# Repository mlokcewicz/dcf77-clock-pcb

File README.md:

# dcf77-clock-pcb

**DCF77-controlled** radio clock PCB based on the **ATmega88** microcontroller, **MAS6181B** AM receiver, and **DS1307** RTC.

**Capabilities:**
* Time and date display
* Alarm handling
* Manual date and time setting
* Automatic periodic synchronization with the DCF77 signal
* Time synchronization status display
* Time zone configuration
* DCF77 signal parameters preview during synchronization
* Time and date data available over the serial port
* Time and date retention powered by a CR2032 battery
  
**Hardware:**
* ATmega88 MCU
* MAS6181B DCF77 receiver
* DS1307 RTC + CR2032
* 2x16 HD44760 LCD
* Rotary Encoder + Button + LED + Buzzer

**Firmware:**
* C11
* Custom MCU peripheral and external circuit drivers

## Tools
* Autodesk EAGLE v9.6.2

## External links
* Firmware repository: https://github.com/mlokcewicz/dcf77-clock

## License
This project is licensed under the CERN Open Hardware Licence Version 2 - Permissive - see the [LICENSE](./LICENSE) file for details.

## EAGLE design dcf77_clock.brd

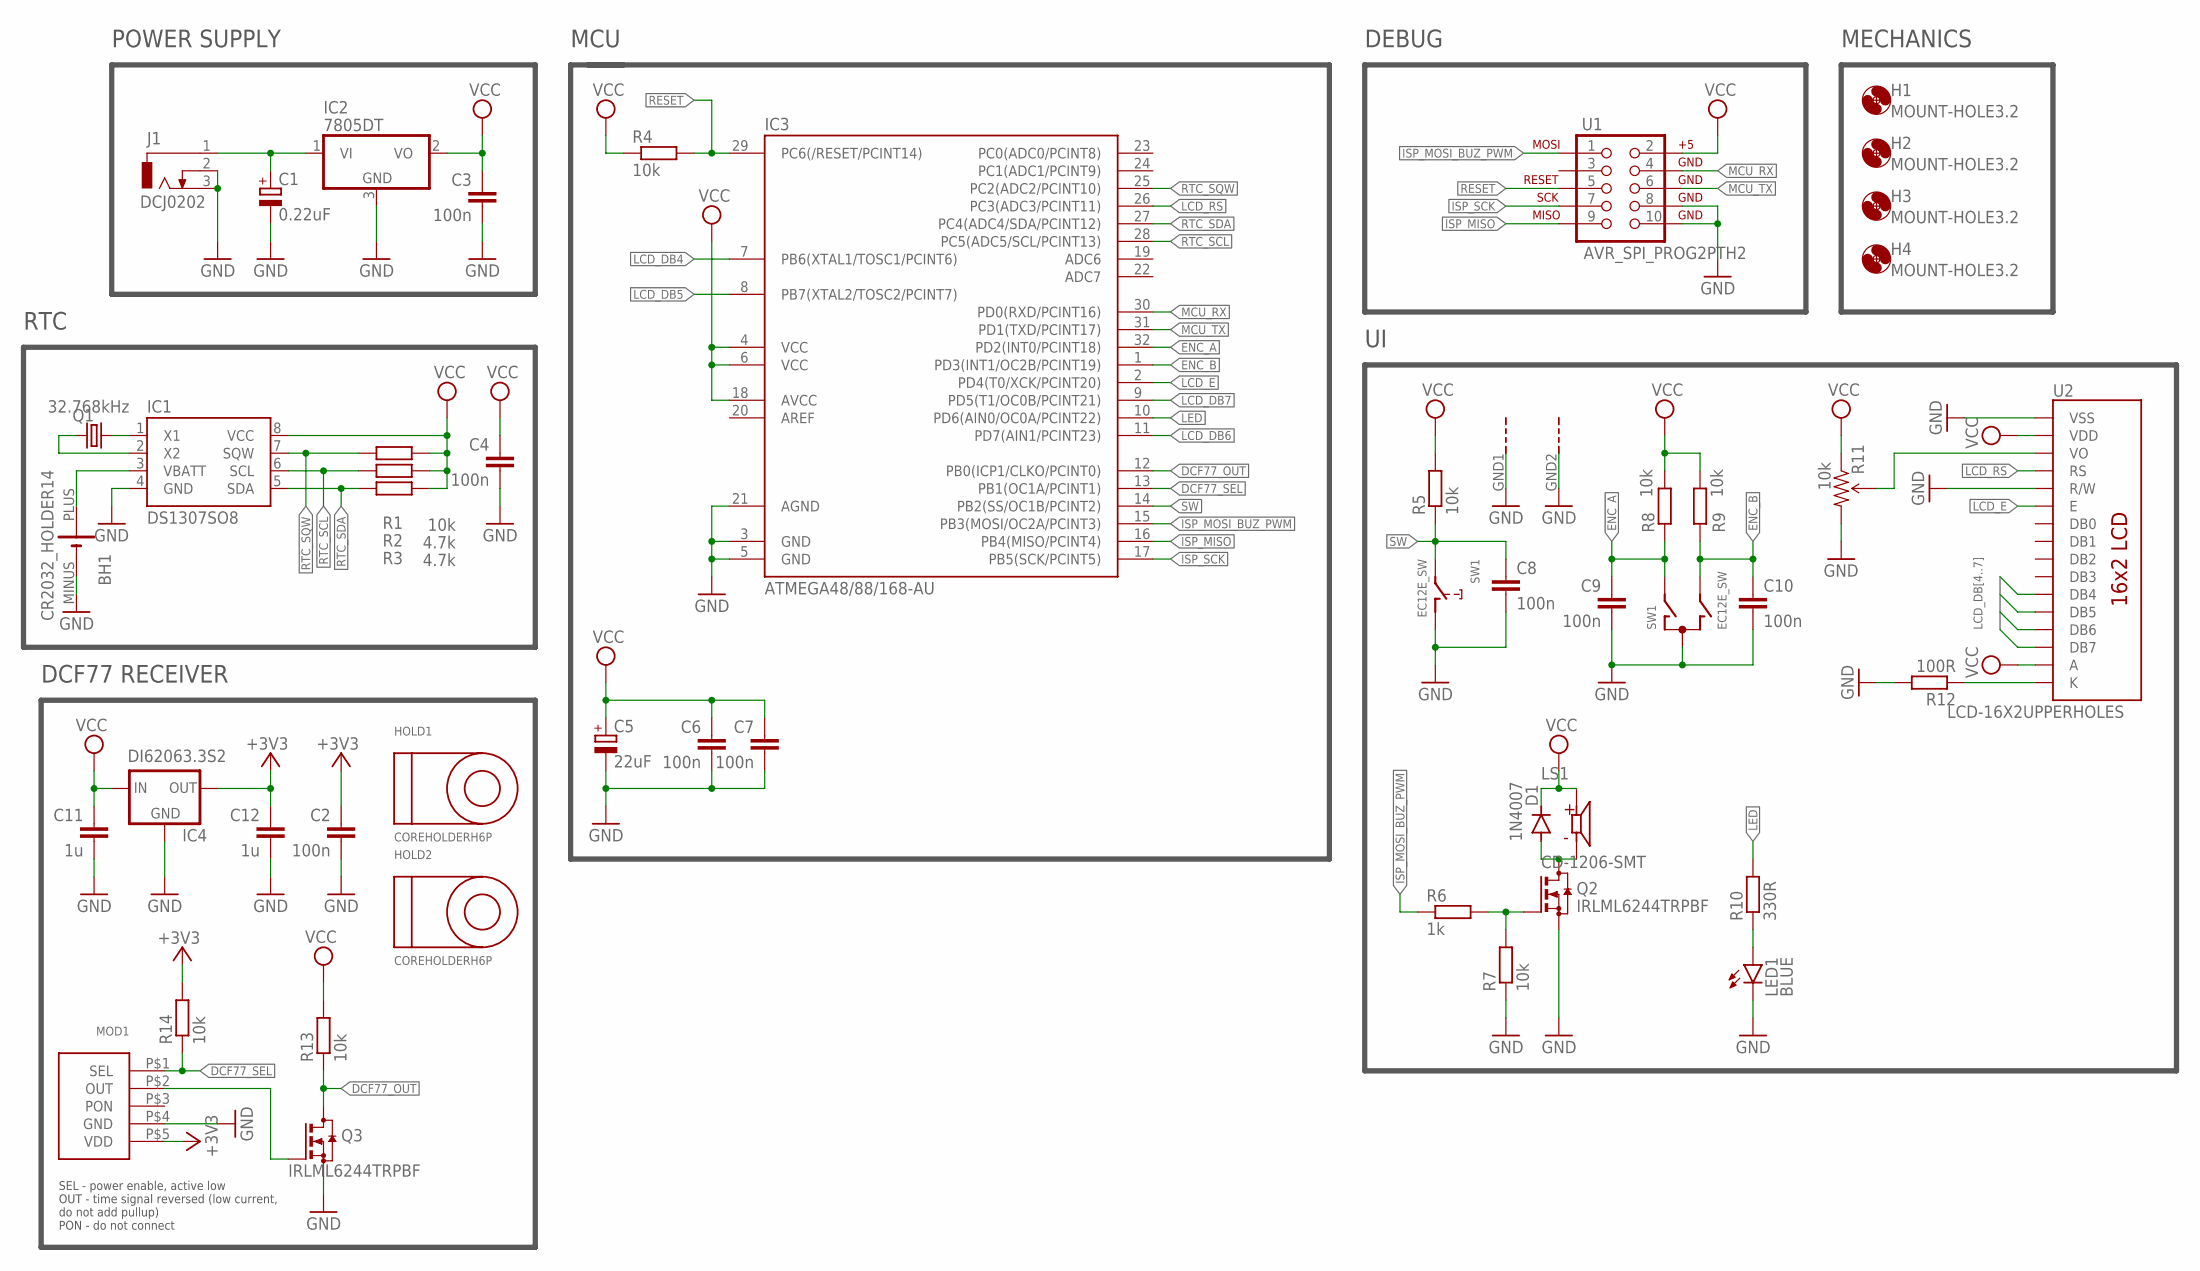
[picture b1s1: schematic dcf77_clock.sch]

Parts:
BH1: CR2032_HOLDER14; CONNFLY-DS1092-14-B6P
C1: 0.22uF; SMC_Z
C2, C3, C4, C6, C7, C8, C9, C10: 100n; C0805K
C5: 22uF; UD-4X5,8_NICHICON
C11, C12: 1u; C0805K
D1: 1N4007; SOD123
H1, H2, H3, H4: MOUNT-HOLE3.2; 3,2
HOLD1, HOLD2: COREHOLDERH6P; H6P
IC1: DS1307SO8; SO08
IC2: 7805DT; TO252
IC3: ATMEGA48/88/168-AU; TQFP32-08
IC4: DI62063.3S2; SOT23
J1: DCJ0202
LED1: BLUE; CHIP-LED0805
LS1: CD-1206-SMT; CUI_CD-1206-SMT
MOD1: DCF77MODULE; DCF77MOD
Q1: 32.768kHz; MM20SS
Q2, Q3: IRLML6244TRPBF; SOT23
R1, R4, R5, R7, R8, R9, R13, R14: 10k; M0805
R2, R3: 4.7k; M0805
R6: 1k; M0805
R10: 330R; M0805
R11: 10k; TRIM_POT_PTH
R12: 100R; M0805
SW1: EC12E_SW; ALPS_EC12E_SW
U1: AVR_SPI_PROG2PTH2; 2X5-SHROUDED
U2: LCD-16X2UPPERHOLES; LCD-16X2_UPPER_HOLES

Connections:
+3V3: C2.1, C12.1, IC4.2 (OUT), MOD1.P$5 (VDD), R14.2
DCF77_OUT: IC3.12 (PB0(ICP1/CLKO/PCINT0)), Q3.3 (D), R13.1
DCF77_SEL: IC3.13 (PB1(OC1A/PCINT1)), MOD1.P$1 (SEL), R14.1
ENC_A: C9.1, IC3.32 (PD2(INT0/PCINT18)), R8.1, SW1.A
ENC_B: C10.1, IC3.1 (PD3(INT1/OC2B/PCINT19)), R9.1, SW1.B
GND: BH1.MINUS, C1.-, C2.2, C3.2, C4.2, C5.-, C6.2, C7.2, C8.2, C9.2, C10.2, C11.2, C12.2, IC1.4 (GND), IC2.3 (GND), IC3.3 (GND), IC3.5 (GND), IC3.21 (AGND), IC4.1 (GND), J1.2, J1.3, LED1.C, MOD1.P$4 (GND), Q2.2 (S), Q3.2 (S), R7.1, R11.3 (CW), R12.2, SW1.C, SW1.D (1), SW1.GND1 (G), SW1.GND2 (G), U1.8, U1.10, U2.1 (VSS), U2.5 (R/W)
ISP_MISO: IC3.16 (PB4(MISO/PCINT4)), U1.9
ISP_MOSI_BUZ_PWM: IC3.15 (PB3(MOSI/OC2A/PCINT3)), R6.1, U1.1
ISP_SCK: IC3.17 (PB5(SCK/PCINT5)), U1.7
LCD_DB4: IC3.7 (PB6(XTAL1/TOSC1/PCINT6)), U2.11 (DB4)
LCD_DB5: IC3.8 (PB7(XTAL2/TOSC2/PCINT7)), U2.12 (DB5)
LCD_DB6: IC3.11 (PD7(AIN1/PCINT23)), U2.13 (DB6)
LCD_DB7: IC3.9 (PD5(T1/OC0B/PCINT21)), U2.14 (DB7)
LCD_E: IC3.2 (PD4(T0/XCK/PCINT20)), U2.6 (E)
LCD_RS: IC3.26 (PC3(ADC3/PCINT11)), U2.4 (RS)
LED: IC3.10 (PD6(AIN0/OC0A/PCINT22)), R10.2
MCU_RX: IC3.30 (PD0(RXD/PCINT16)), U1.4
MCU_TX: IC3.31 (PD1(TXD/PCINT17)), U1.6
unnamed: C1.+, IC2.1 (VI), J1.1
unnamed: D1.A, LS1.M, Q2.3 (D)
unnamed: Q2.1 (G), R6.2, R7.2
unnamed: LED1.A, R10.1
unnamed: MOD1.P$2 (OUT), Q3.1 (G)
unnamed: R11.2 (WIPER), U2.3 (VO)
unnamed: R12.1, U2.16 (K)
unnamed: IC1.1 (X1), Q1.1
unnamed: IC1.2 (X2), Q1.4 (2)
unnamed: BH1.PLUS, IC1.3 (VBATT)
RESET: IC3.29 (PC6(/RESET/PCINT14)), R4.2, U1.5
RTC_SCL: IC1.6 (SCL), IC3.28 (PC5(ADC5/SCL/PCINT13)), R2.2
RTC_SDA: IC1.5 (SDA), IC3.27 (PC4(ADC4/SDA/PCINT12)), R3.2
RTC_SQW: IC1.7 (SQW), IC3.25 (PC2(ADC2/PCINT10)), R1.2
SW: C8.1, IC3.14 (PB2(SS/OC1B/PCINT2)), R5.1, SW1.E (2)
VCC: C3.1, C4.1, C5.+, C6.1, C7.1, C11.1, D1.C, IC1.8 (VCC), IC2.2 (VO), IC3.4 (VCC), IC3.6 (VCC), IC3.18 (AVCC), IC4.3 (IN), LS1.P, R1.1, R2.1, R3.1, R4.1, R5.2, R8.2, R9.2, R11.1 (CCW), R13.2, U1.2, U2.2 (VDD), U2.15 (A)

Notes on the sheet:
POWER SUPPLY
MCU
DEBUG
MECHANICS
RTC
DCF77 RECEIVER
SEL - power enable, active low OUT - time signal reversed (low current, do not add pullup) PON - do not connect

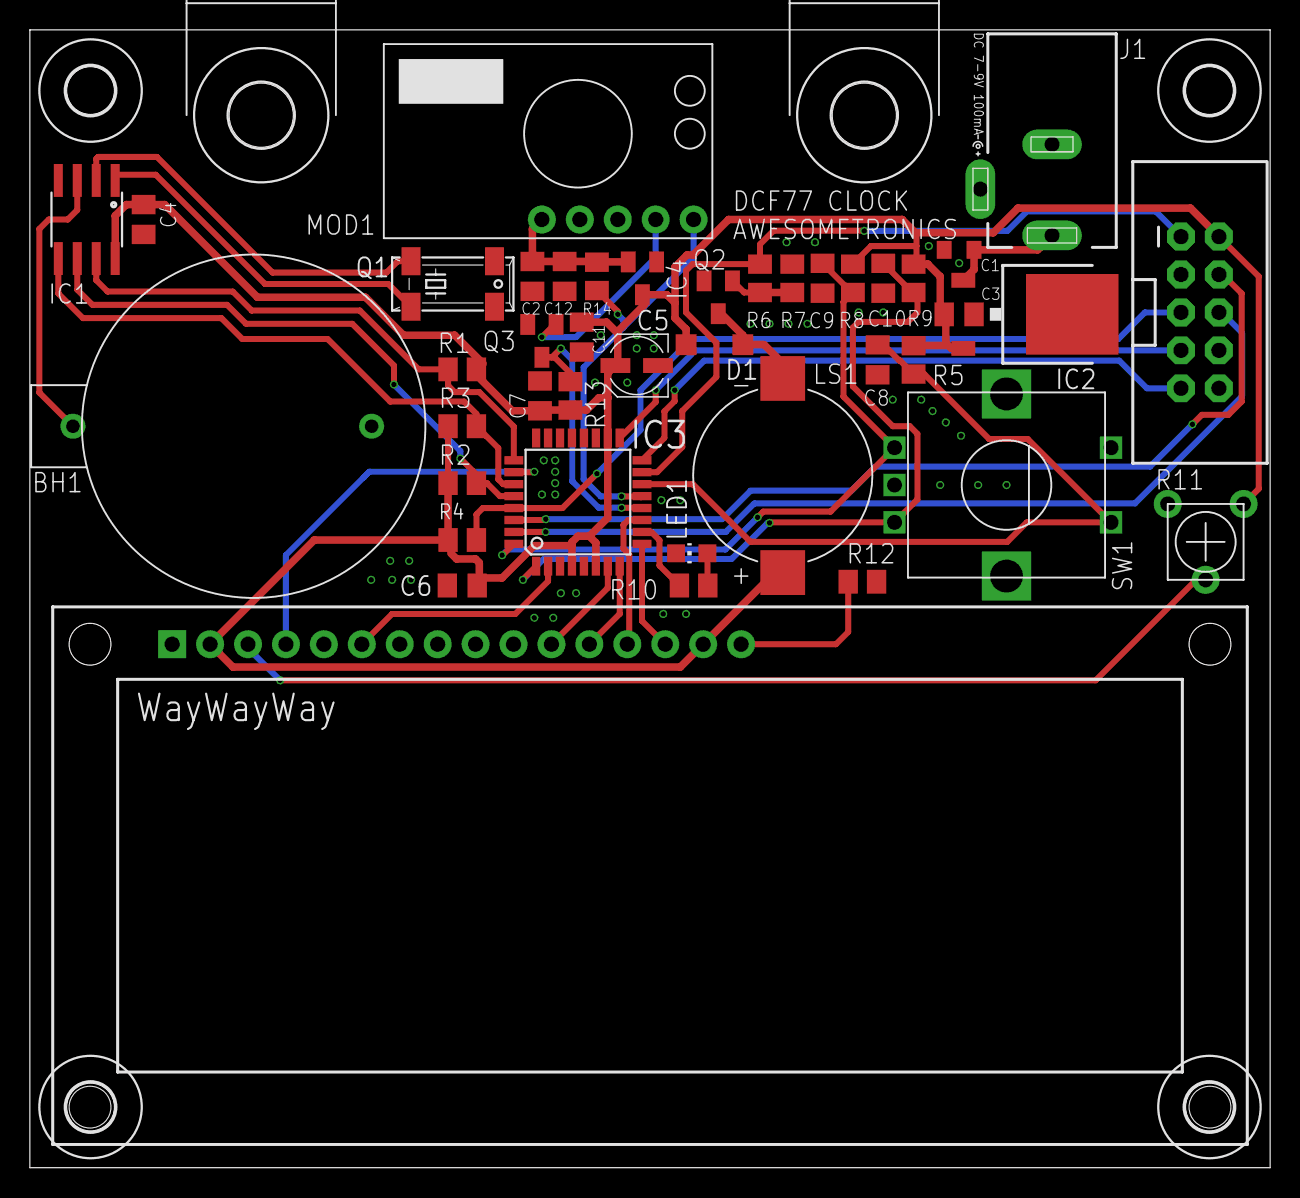
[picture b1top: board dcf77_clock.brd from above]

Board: 2 copper layers, 83.1 x 76.2 mm, 48 parts (0 on the bottom side), 34 nets.

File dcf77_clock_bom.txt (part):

Partlist exported from D:/Elektronika/Repozytoria/GitHub/hardware/dcf77-clock-pcb/dcf77_clock.sch at 09.04.2025 18:27

Qty Value              Device             Package               Parts                            Description                                  AVAILABILITY CUI_PURCHASE_URL                                                                                                                              DESCRIPTION                                                                      MF       MP             MPN          OC_FARNELL OC_NEWARK PACKAGE  POPULARITY PRICE SPICEPREFIX
1   0.22uF             CPOL-EUSMCZ        SMC_Z                 C1                               POLARIZED CAPACITOR, European symbol                                                                                                                                                                                                                                                                                                                        0                C          
1   100R               R-EU_M0805         M0805                 R12                              RESISTOR, European symbol                                                                                                                                                                                                                                                                                                                                   45               R          
8   100n               C-EUC0805K         C0805K                C2, C3, C4, C6, C7, C8, C9, C10  CAPACITOR, European symbol                                                                                                                                                                                                                                                                                                                                  52               C          
8   10k                R-EU_M0805         M0805                 R1, R4, R5, R7, R8, R9, R13, R14 RESISTOR, European symbol                                                                                                                                                                                                                                                                                                                                   45               R          
1   10k                TRIMPOTPTH         TRIM_POT_PTH          R11                                                                                                                                                                                                                                                                                                                                                                                                                      
1   1N4007             DIODE-SOD123       SOD123                D1                               DIODE                                                                                                                                                                                                                                                                                                                                                       22                          
1   1k                 R-EU_M0805         M0805                 R6                               RESISTOR, European symbol                                                                                                                                                                                                                                                                                                                                   45               R          
2   1u                 C-EUC0805K         C0805K                C11, C12                         CAPACITOR, European symbol                                                                                                                                                                                                                                                                                                                                  52               C          
1   22uF               CPOL-EUUD-4X5,8    UD-4X5,8_NICHICON     C5                               POLARIZED CAPACITOR, European symbol                                                                                                                                                                                                                                                                                                                        0                C          
1   32.768kHz          CRYSTALMM20SS      MM20SS                Q1                               CRYSTAL                                                                                                                                                                                                                                                                                                                       unknown    unknown            4                           
1   330R               R-EU_M0805         M0805                 R10                              RESISTOR, European symbol                                                                                                                                                                                                                                                                                                                                   45               R          
2   4.7k               R-EU_M0805         M0805                 R2, R3                           RESISTOR, European symbol                                                                                                                                                                                                                                                                                                                                   45               R          
1   7805DT             7805DT             TO252                 IC2                              Positive VOLTAGE REGULATOR                                                                                                                                                                                                                                                                                                                                  0                           
1   ATMEGA48/88/168-AU ATMEGA48/88/168-AU TQFP32-08             IC3                                                                                                                                                                                                                                                                                                                                                                                                                      
1   AVR_SPI_PROG2PTH2  AVR_SPI_PROG2PTH2  2X5-SHROUDED          U1                               AVR ICSP Header                                                                                                                                                                                                                                                                                                                                                                         
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
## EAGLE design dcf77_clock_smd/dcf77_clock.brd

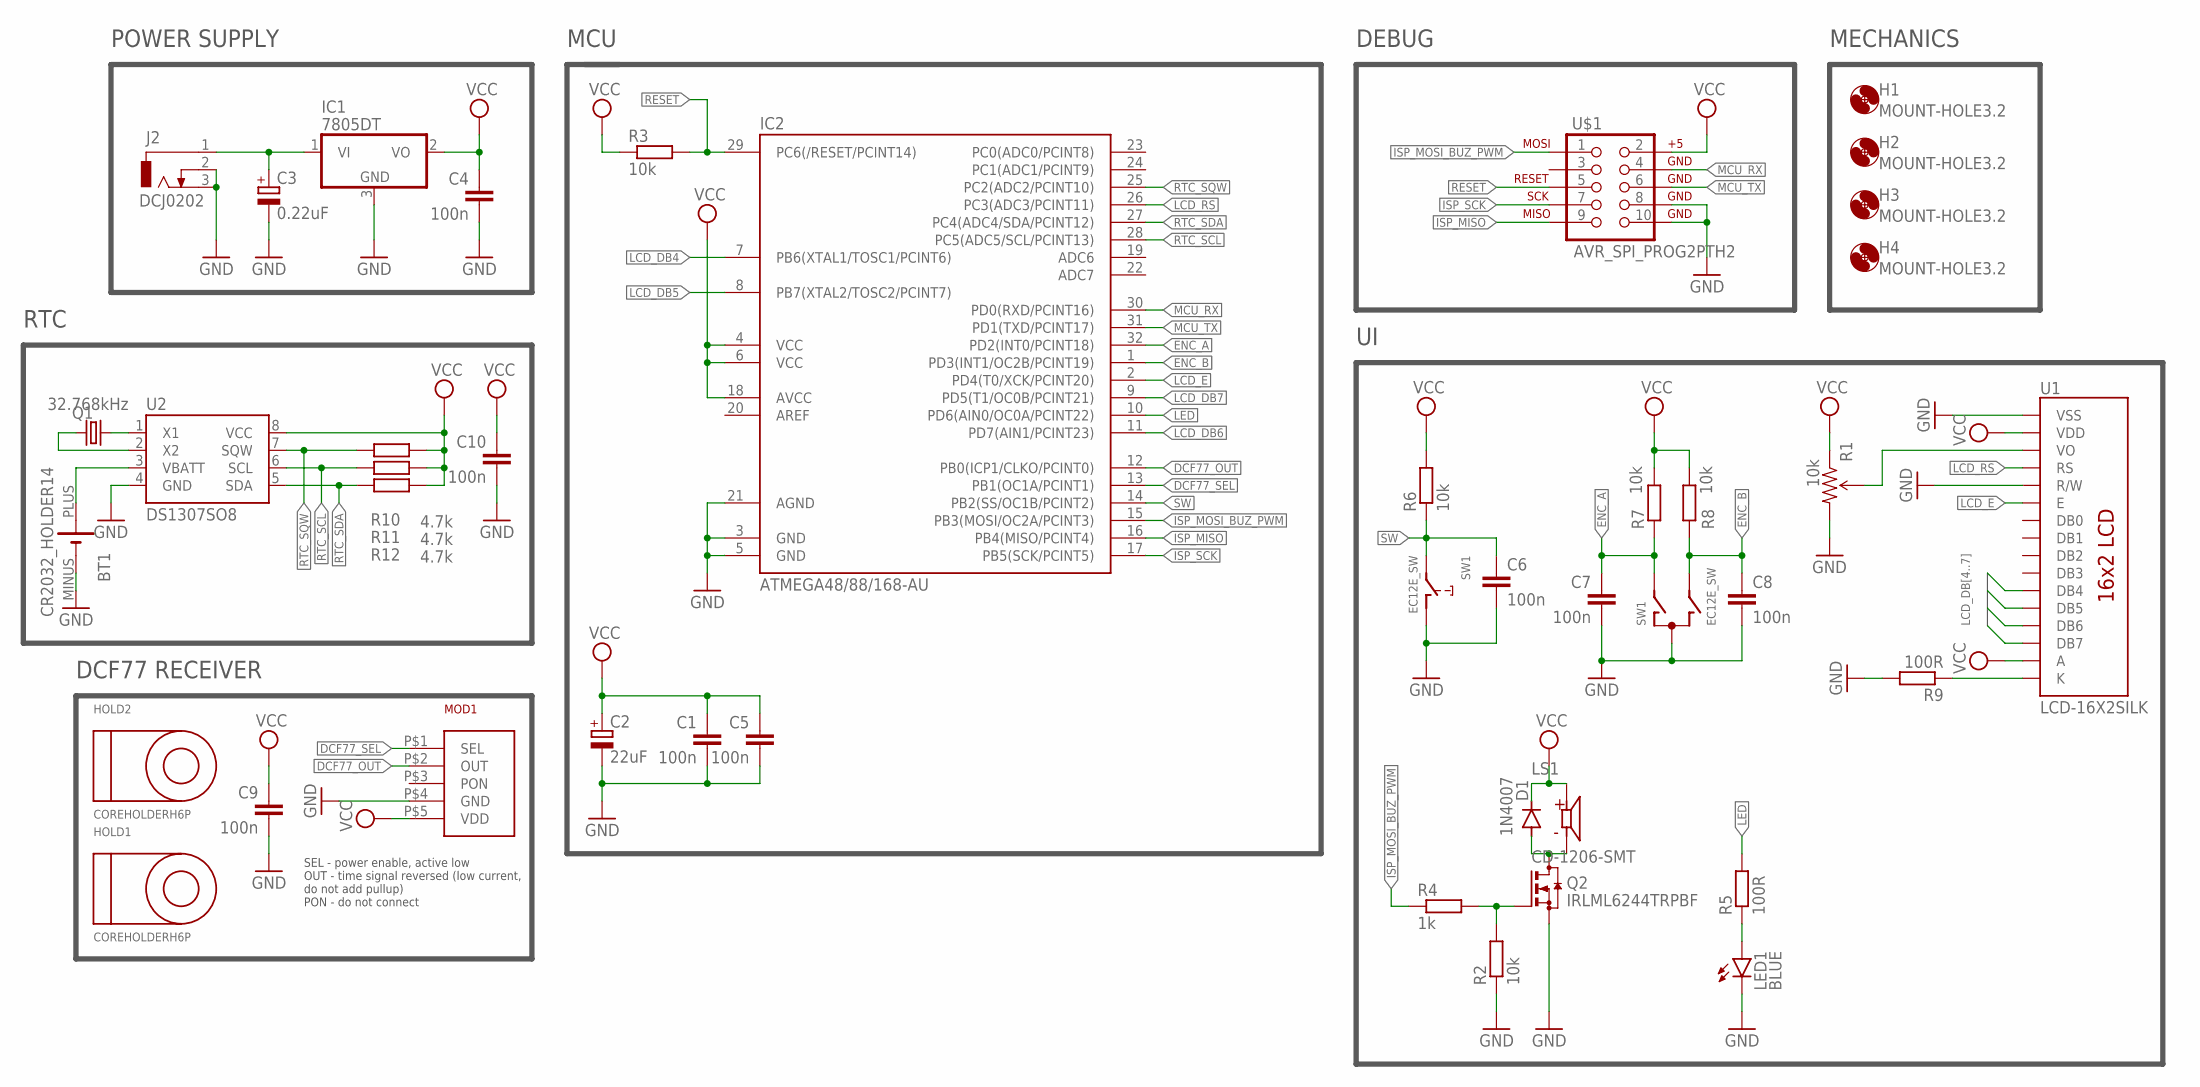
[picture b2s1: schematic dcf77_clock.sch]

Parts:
BT1: CR2032_HOLDER14; CONNFLY-DS1092-14-B6P
C1, C4, C5, C6, C7, C8, C9, C10: 100n; C0805K
C2: 22uF; UD-4X5,8_NICHICON
C3: 0.22uF; SMC_Z
D1: 1N4007; SOD123
H1, H2, H3, H4: MOUNT-HOLE3.2; 3,2
HOLD1, HOLD2: COREHOLDERH6P; H6P
IC1: 7805DT; TO252
IC2: ATMEGA48/88/168-AU; TQFP32-08
J2: DCJ0202
LED1: BLUE; CHIP-LED0805
LS1: CD-1206-SMT; CUI_CD-1206-SMT
MOD1: DCF77MODULE; DCF77MOD
Q1: 32.768kHz; MM20SS
Q2: IRLML6244TRPBF; SOT23
R1: 10k; TRIM_POT_PTH
R2, R3, R6, R7, R8: 10k; M0805
R4: 1k; M0805
R5, R9: 100R; M0805
R10, R11, R12: 4.7k; M0805
SW1: EC12E_SW; ALPS_EC12E_SW
U1: LCD-16X2SILK; LCD-16X2
U2: DS1307SO8; SO08
U$1: AVR_SPI_PROG2PTH2; 2X5-SHROUDED

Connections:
DCF77_OUT: IC2.12 (PB0(ICP1/CLKO/PCINT0)), MOD1.P$2 (OUT)
DCF77_SEL: IC2.13 (PB1(OC1A/PCINT1)), MOD1.P$1 (SEL)
ENC_A: C7.1, IC2.32 (PD2(INT0/PCINT18)), R7.1, SW1.A
ENC_B: C8.1, IC2.1 (PD3(INT1/OC2B/PCINT19)), R8.1, SW1.B
GND: BT1.MINUS, C1.2, C2.-, C3.-, C4.2, C5.2, C6.2, C7.2, C8.2, C9.2, C10.2, IC1.3 (GND), IC2.3 (GND), IC2.5 (GND), IC2.21 (AGND), J2.2, J2.3, LED1.C, MOD1.P$4 (GND), Q2.2 (S), R1.3 (CW), R2.1, R9.2, SW1.C, SW1.D (1), U1.1 (VSS), U1.5 (R/W), U2.4 (GND), U$1.8, U$1.10
ISP_MISO: IC2.16 (PB4(MISO/PCINT4)), U$1.9
ISP_MOSI_BUZ_PWM: IC2.15 (PB3(MOSI/OC2A/PCINT3)), R4.1, U$1.1
ISP_SCK: IC2.17 (PB5(SCK/PCINT5)), U$1.7
LCD_DB4: IC2.7 (PB6(XTAL1/TOSC1/PCINT6)), U1.11 (DB4)
LCD_DB5: IC2.8 (PB7(XTAL2/TOSC2/PCINT7)), U1.12 (DB5)
LCD_DB6: IC2.11 (PD7(AIN1/PCINT23)), U1.13 (DB6)
LCD_DB7: IC2.9 (PD5(T1/OC0B/PCINT21)), U1.14 (DB7)
LCD_E: IC2.2 (PD4(T0/XCK/PCINT20)), U1.6 (E)
LCD_RS: IC2.26 (PC3(ADC3/PCINT11)), U1.4 (RS)
LED: IC2.10 (PD6(AIN0/OC0A/PCINT22)), R5.2
MCU_RX: IC2.30 (PD0(RXD/PCINT16)), U$1.4
MCU_TX: IC2.31 (PD1(TXD/PCINT17)), U$1.6
unnamed: C3.+, IC1.1 (VI), J2.1
unnamed: D1.A, LS1.M, Q2.3 (D)
unnamed: Q2.1 (G), R2.2, R4.2
unnamed: LED1.A, R5.1
unnamed: R1.2 (WIPER), U1.3 (VO)
unnamed: R9.1, U1.16 (K)
unnamed: Q1.1, U2.1 (X1)
unnamed: Q1.4 (2), U2.2 (X2)
unnamed: BT1.PLUS, U2.3 (VBATT)
RESET: IC2.29 (PC6(/RESET/PCINT14)), R3.2, U$1.5
RTC_SCL: IC2.28 (PC5(ADC5/SCL/PCINT13)), R11.2, U2.6 (SCL)
RTC_SDA: IC2.27 (PC4(ADC4/SDA/PCINT12)), R12.2, U2.5 (SDA)
RTC_SQW: IC2.25 (PC2(ADC2/PCINT10)), R10.2, U2.7 (SQW)
SW: C6.1, IC2.14 (PB2(SS/OC1B/PCINT2)), R6.1, SW1.E (2)
VCC: C1.1, C2.+, C4.1, C5.1, C9.1, C10.1, D1.C, IC1.2 (VO), IC2.4 (VCC), IC2.6 (VCC), IC2.18 (AVCC), LS1.P, MOD1.P$5 (VDD), R1.1 (CCW), R3.1, R6.2, R7.2, R8.2, R10.1, R11.1, R12.1, U1.2 (VDD), U1.15 (A), U2.8 (VCC), U$1.2

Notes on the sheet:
POWER SUPPLY
MCU
DEBUG
MECHANICS
RTC
DCF77 RECEIVER
SEL - power enable, active low OUT - time signal reversed (low current, do not add pullup) PON - do not connect

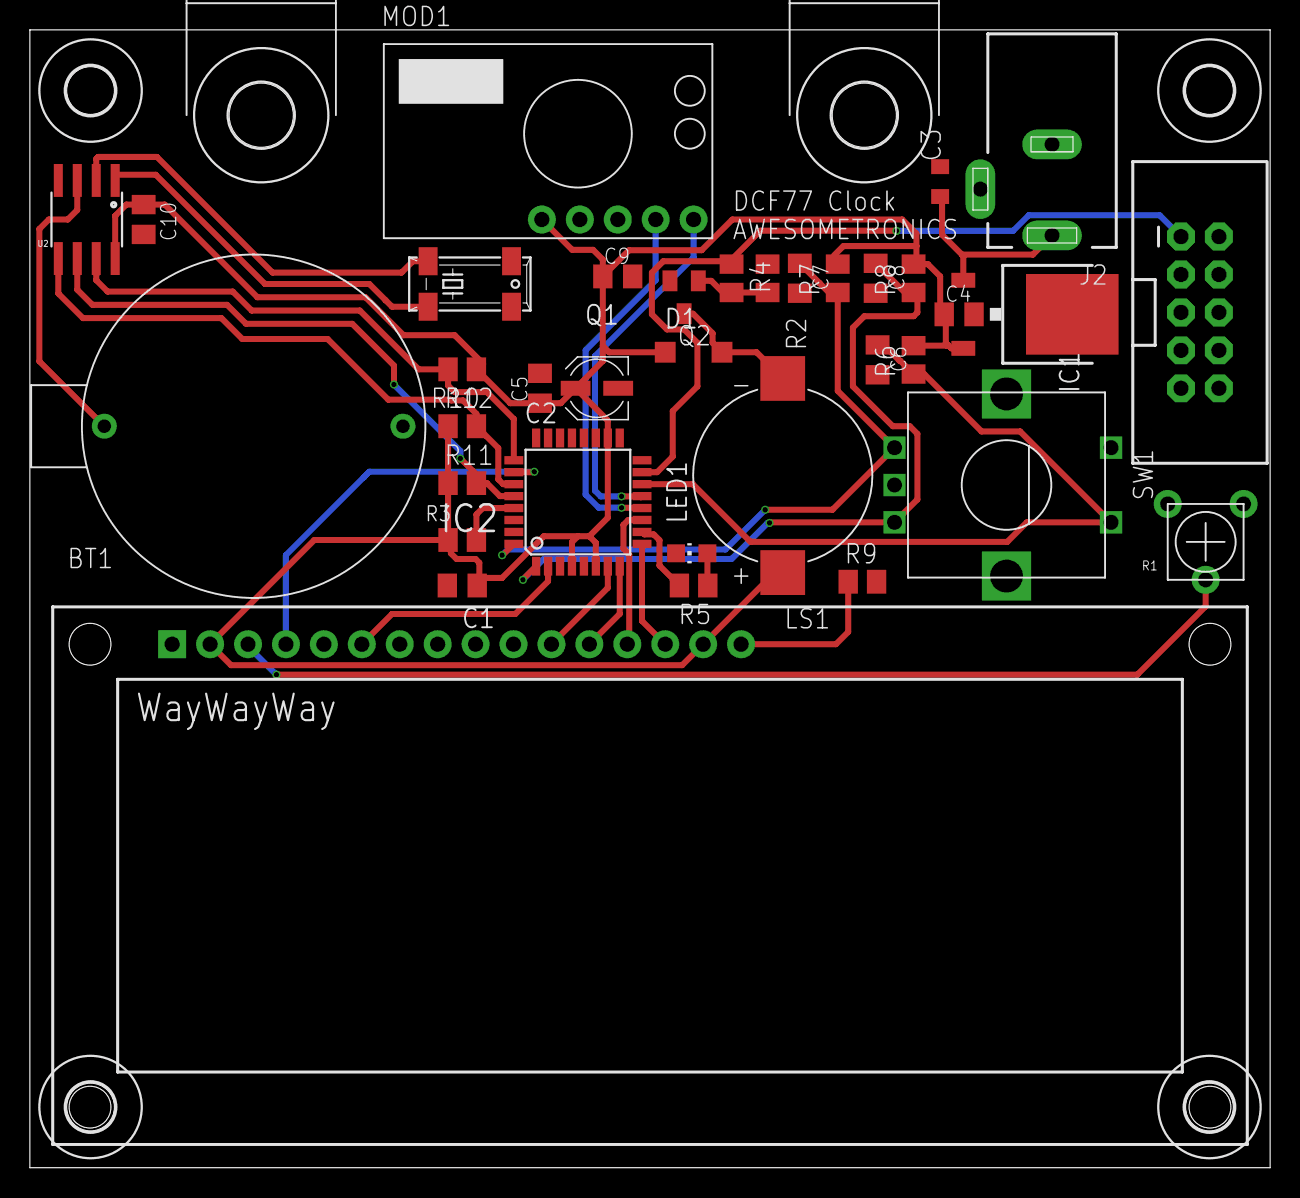
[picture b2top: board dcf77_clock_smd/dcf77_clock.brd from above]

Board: 2 copper layers, 83.1 x 76.2 mm, 42 parts (0 on the bottom side), 32 nets.

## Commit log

2025-03-18 Add THT and SMD draft
2025-03-18 Update capacitors footprints
2025-03-19 Add power supply and basic components schematic
2025-03-20 Add first complete version of schematic
2025-03-20 ERC fixes
2025-03-21 Rearrange I2C pullups
2025-03-21 Add BOM
2025-03-21 Change buzzer footprint
2025-03-22 Allign mounting holes
2025-03-22 Replace incorrect footprints
2025-03-22 Change oscillator footprint
2025-03-23 Add encoder connections
2025-03-23 Move to parent directory
2025-03-23 Finish signal and VCC routing
2025-03-23 Add GND polygon and missing vias
2025-03-23 Place hidden encoder pins and connect to GND
2025-03-23 DRC checked
2025-03-23 Add Gerber files
2025-03-27 Add 3V3 LDO and level shifter for MAS6181B
2025-03-27 Maximize DC supply info
2025-03-27 Fit DC power supply info
2025-03-27 Add JLCPCB gerber files
2025-03-27 Fix DCF77 IC name
2025-04-07 Fix CR2032 holder footprint
2025-04-09 Change LED resistor to limit brightness
2025-04-12 Add images
2025-04-12 Add image
2025-05-24 Add final picture
2025-05-24 Add assembled photo
2025-05-24 Create LICENSE

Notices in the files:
parts and their libraries:
SparkFun: Licensing: CC v3.0 Share-Alike You are welcome to use this library for commercial purposes.
